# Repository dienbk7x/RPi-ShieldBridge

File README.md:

# RPi-ShieldBridge
Raspberry Pi 1 A/B to Uno Shield Bridge.

## Shop
* [RPi-ShieldBridge for Raspberry Pi 1 Model A and B](http://www.watterott.com/en/RPi-ShieldBridge)

## Features
* Atmel AVR ATmega328 with Arduino compatible Bootloader (optiboot)
* Raspberry Pi connected via I2C and UART (to the AVR through level-shifter)
* AVR-Programming via Raspberry Pi possible
* Shield connectors with Uno R3 layout
* Additional 3.3V LDO voltage regulator for Shields
* Prototyping Area
* Optional MI0283QT-Adapter (2.8" 320x240 Display with Touchscreen/Touchpanel)
* Optional 3-11V power input for Raspberry Pi and ShieldBridge (Pololu S7V7F5)

## Hardware
* 
* [Schematics + Layout](https://github.com/watterott/RPi-ShieldBridge/tree/master/hardware)

## Software
* [How to install the Arduino IDE on Raspberry Pi](https://github.com/watterott/RPi-ShieldBridge/blob/master/docu/Arduino.md)
* [How to control the RPi-ShieldBridge with Firmata](https://github.com/watterott/RPi-ShieldBridge/blob/master/docu/Firmata.md)
* [How to communicate with the RPi-ShieldBridge via I2C](https://github.com/watterott/RPi-ShieldBridge/blob/master/docu/I2CTest.md)
* [How to use a MI0283QT-Adapter (2.8" Display with Touchpanel)](https://github.com/watterott/RPi-ShieldBridge/blob/master/docu/MI0283QT-Adapter.md)
* [Nuage a Arduino Yún compatible device](http://www.arduino-hausautomation.de/nuage/)

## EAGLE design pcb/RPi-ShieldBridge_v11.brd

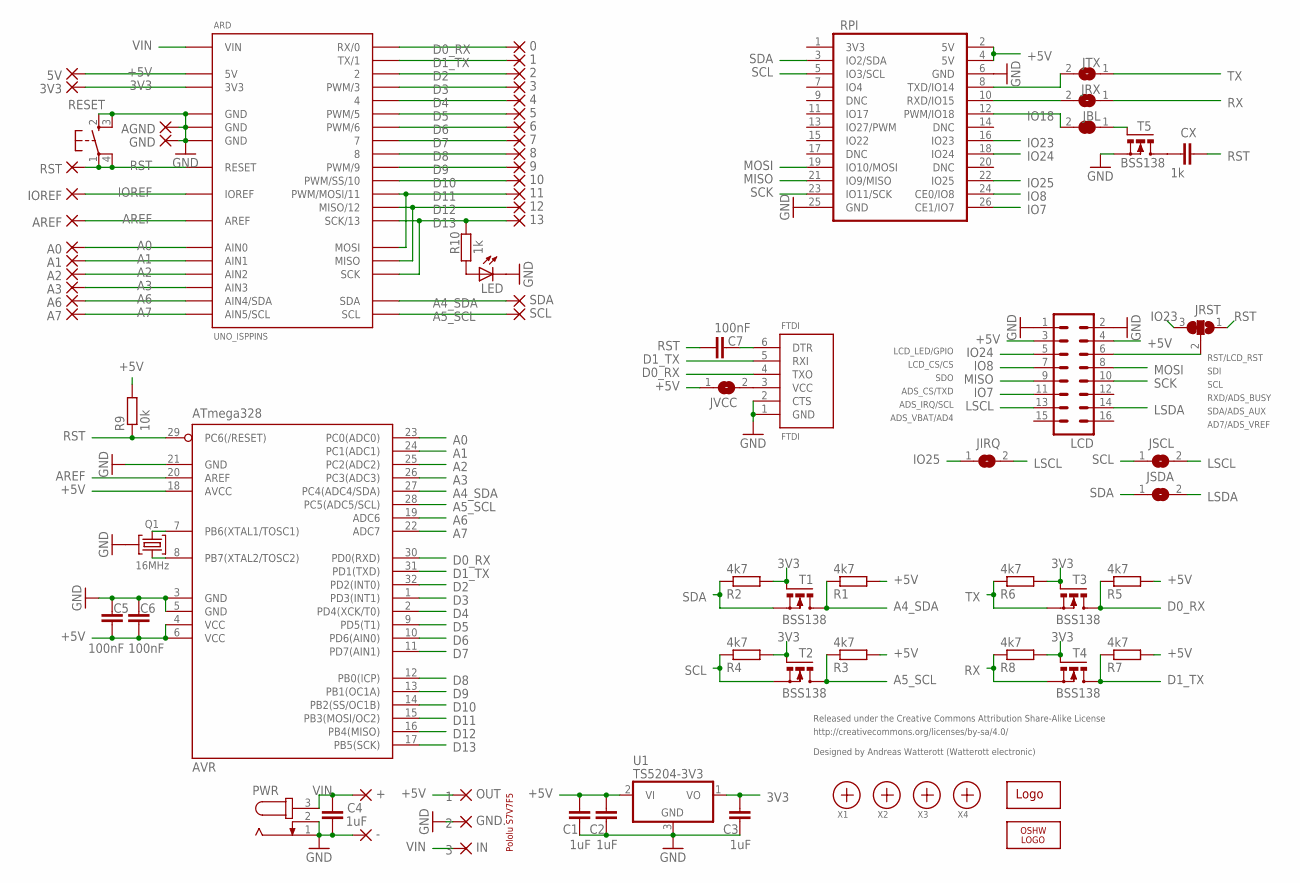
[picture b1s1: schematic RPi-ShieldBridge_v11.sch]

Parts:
0, 1, 2, 3, 3V3, 4, 5, 5V, 6, 7, 8, 9, 10, 11, 12, 13: WIREPAD1,6/0,9; 1,6/0,9
+: WIREPAD2,54/1,0; 2,54/1,0
-: WIREPAD2,54/1,0; 2,54/1,0
A0, A1, A2, A3, A6, A7: WIREPAD1,6/0,9; 1,6/0,9
AGND: WIREPAD1,6/0,9; 1,6/0,9
ARD: UNO_ISPPINS; UNO_ISP3
AREF: WIREPAD1,6/0,9; 1,6/0,9
AVR: ATmega328; TQFP32-08
C1, C2, C3, C4: 1uF; C0603
C5, C6, C7: 100nF; C0603
CX: 1k; C0603
FTDI: FTDI
GND: WIREPAD1,6/0,9; 1,6/0,9
GND.: 2; 1,6/0,9
IN: 3; 1,6/0,9
IOREF: WIREPAD1,6/0,9; 1,6/0,9
JBL: SJ
JIRQ: SJ
JRST: SJ2W; SJ_2
JRX: SJ
JSCL: SJ
JSDA: SJ
JTX: SJ
JVCC: SJ
LCD: MA08-2
LED: LEDCHIPLED_0603; CHIPLED_0603
LOGO1: OSHW_LOGO_6MILX0150-NT; OSHW_6X150_NOTEXT
OUT: 1; 1,6/0,9
PWR: DC-JACK""; DC-JACK
Q1: 16MHz; SMD_OSC_35X15
R1, R2, R3, R4, R5, R6, R7, R8: 4k7; R0603
R9: 10k; R0603
R10: 1k; R0603
RESET: SW_SMDS; SW_SMD4@1
RPI: RPI
RST: WIREPAD1,6/0,9; 1,6/0,9
SCL: WIREPAD1,6/0,9; 1,6/0,9
SDA: WIREPAD1,6/0,9; 1,6/0,9
T1, T2, T3, T4, T5: BSS138; MICRO3
U1: TS5204-3V3; SOT23
U$1: WE-LOGO
X1, X2, X3, X4: PASSER

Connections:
3V3: 3V3.1, ARD.3V3, C3.1, R2.2, R4.2, R6.2, R8.2, T1.1 (G), T2.1 (G), T3.1 (G), T4.1 (G), U1.1 (VO)
+5V: 5V.1, ARD.5V, AVR.4 (VCC), AVR.6 (VCC), AVR.18 (AVCC), C1.1, C2.1, C5.1, C6.1, JVCC.1, LCD.3, LCD.4, OUT.1, R1.2, R3.2, R5.2, R7.2, R9.2, RPI.2 (5V), RPI.4 (5V), U1.2 (VI)
A0: A0.1, ARD.AIN0, AVR.23 (PC0(ADC0))
A1: A1.1, ARD.AIN1, AVR.24 (PC1(ADC1))
A2: A2.1, ARD.AIN2, AVR.25 (PC2(ADC2))
A3: A3.1, ARD.AIN3, AVR.26 (PC3(ADC3))
A4_SDA: ARD.SDA, AVR.27 (PC4(ADC4/SDA)), R1.1, SDA.1, T1.3 (D)
A5_SCL: ARD.SCL, AVR.28 (PC5(ADC5/SCL)), R3.1, SCL.1, T2.3 (D)
A6: A6.1, ARD.AIN4 (AIN4/SDA), AVR.19 (ADC6)
A7: A7.1, ARD.AIN5 (AIN5/SCL), AVR.22 (ADC7)
AREF: ARD.AREF, AREF.1, AVR.20 (AREF)
D0_RX: 0.1, ARD.0 (RX/0), AVR.30 (PD0(RXD)), FTDI.4 (TXO), R5.1, T3.3 (D)
D1_TX: 1.1, ARD.1 (TX/1), AVR.31 (PD1(TXD)), FTDI.5 (RXI), R7.1, T4.3 (D)
D2: 2.1, ARD.2, AVR.32 (PD2(INT0))
D3: 3.1, ARD.3 (PWM/3), AVR.1 (PD3(INT1))
D4: 4.1, ARD.4, AVR.2 (PD4(XCK/T0))
D5: 5.1, ARD.5 (PWM/5), AVR.9 (PD5(T1))
D6: 6.1, ARD.6 (PWM/6), AVR.10 (PD6(AIN0))
D7: 7.1, ARD.7, AVR.11 (PD7(AIN1))
D8: 8.1, ARD.8, AVR.12 (PB0(ICP))
D9: 9.1, ARD.9 (PWM/9), AVR.13 (PB1(OC1A))
D10: 10.1, ARD.10 (PWM/SS/10), AVR.14 (PB2(SS/OC1B))
D11: 11.1, ARD.11 (PWM/MOSI/11), ARD.MOSI, AVR.15 (PB3(MOSI/OC2))
D12: 12.1, ARD.12 (MISO/12), ARD.MISO, AVR.16 (PB4(MISO))
D13: 13.1, ARD.13 (SCK/13), ARD.SCK, AVR.17 (PB5(SCK)), R10.1
DTR: C7.1, FTDI.6 (DTR)
GND: -.1, AGND.1, ARD.GND@1 (GND), ARD.GND@2 (GND), ARD.GND@3 (GND), AVR.3 (GND), AVR.5 (GND), AVR.21 (GND), C1.2, C2.2, C3.2, C4.2, C5.2, C6.2, FTDI.1 (GND), FTDI.2 (CTS), GND.1, GND..1, LCD.1, LCD.2, LED.C, PWR.1, PWR.2, Q1.GND, RESET.2 (S), RESET.3 (S1), RPI.6 (GND), RPI.25 (GND), T5.2 (S), U1.3 (GND)
IO7: LCD.11, RPI.26 (CE1/IO7)
IO8: LCD.7, RPI.24 (CE0/IO8)
IO18: JBL.2, RPI.12 (PWM/IO18)
IO23: JRST.3, RPI.16 (IO23)
IO24: LCD.5, RPI.18 (IO24)
IO25: JIRQ.1, RPI.22 (IO25)
IOREF: ARD.IOREF, IOREF.1
LCD_RST: JRST.2, LCD.6
LSCL: JIRQ.2, JSCL.2, LCD.13
LSDA: JSDA.2, LCD.14
MISO: LCD.9, RPI.21 (IO9/MISO)
MOSI: LCD.8, RPI.19 (IO10/MOSI)
unnamed: AVR.8 (PB7(XTAL2/TOSC2)), Q1.2
unnamed: AVR.7 (PB6(XTAL1/TOSC1)), Q1.1
unnamed: CX.1, T5.3 (D)
unnamed: LED.A, R10.2
RPI_RST: JBL.1, T5.1 (G)
RST: ARD.RST (RESET), AVR.29 (PC6(/RESET)), C7.2, CX.2, JRST.1, R9.1, RESET.1, RESET.4 (P1), RST.1
RX: JRX.1, R8.1, T4.2 (S)
RX_IO15: JRX.2, RPI.10 (RXD/IO15)
SCK: LCD.10, RPI.23 (IO11/SCK)
SCL: JSCL.1, R4.1, RPI.5 (IO3/SCL), T2.2 (S)
SDA: JSDA.1, R2.1, RPI.3 (IO2/SDA), T1.2 (S)
TX: JTX.1, R6.1, T3.2 (S)
TX_IO14: JTX.2, RPI.8 (TXD/IO14)
VCC: FTDI.3 (VCC), JVCC.2
VIN: +.1, ARD.VIN, C4.1, IN.1, PWR.3

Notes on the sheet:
LCD_LED/GPIO
LCD_CS/CS
SDO
ADS_CS/TXD
ADS_IRQ/SCL
ADS_VBAT/AD4
AD7/ADS_VREF
SDA/ADS_AUX
RXD/ADS_BUSY
SCL
SDI
RST/LCD_RST
Pololu S7V7F5
Released under the Creative Commons Attribution Share-Alike License
http://creativecommons.org/licenses/by-sa/4.0/
Designed by Andreas Watterott (Watterott electronic)

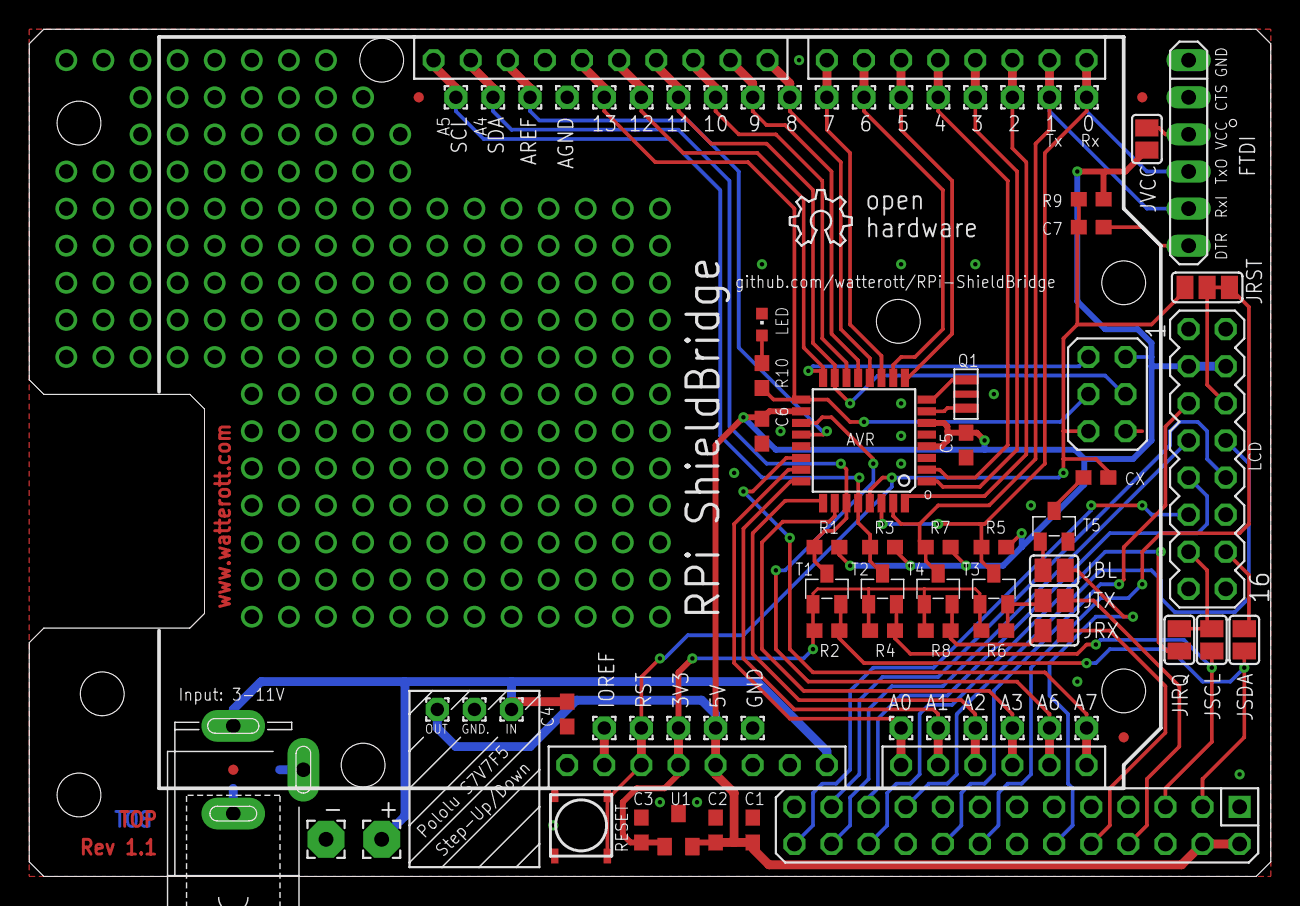
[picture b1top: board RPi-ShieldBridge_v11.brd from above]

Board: 2 copper layers, 85.0 x 58.0 mm, 81 parts (1 on the bottom side), 54 nets.

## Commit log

2013-07-01 added rev 1.0 schematic and layout
2013-07-03 added docu
2013-07-04 added image
2013-07-31 updated docu
2013-08-01 added v1.1 pcb
2013-08-11 updated v1.1
2013-08-18 updated readme and image
2013-08-18 updated firmata guide
2013-09-21 added hardware diagram
2013-10-01 updated image
2013-10-12 updated MI0283QT-Adapter docu
2013-10-12 added I2C communication example
2013-10-12 added Arduino install guide
2013-10-12 updated docu and readme
2013-11-13 updated MI0283QT docu
2013-12-10 FBTFT: MI0283QT2 parameter corrected
2014-03-05 Eagle v6 format
2014-08-15 updated schematic and layout files
2014-08-21 updated layout and schematics
2014-11-06 cleaned up schematics and layout
2015-04-24 moved image
2015-08-21 changed path structure
2015-09-16 updated autoreset
2015-10-05 updated autoreset (timout bugfix)
2015-12-04 moved info message to the start
2016-04-10 updated schematics
